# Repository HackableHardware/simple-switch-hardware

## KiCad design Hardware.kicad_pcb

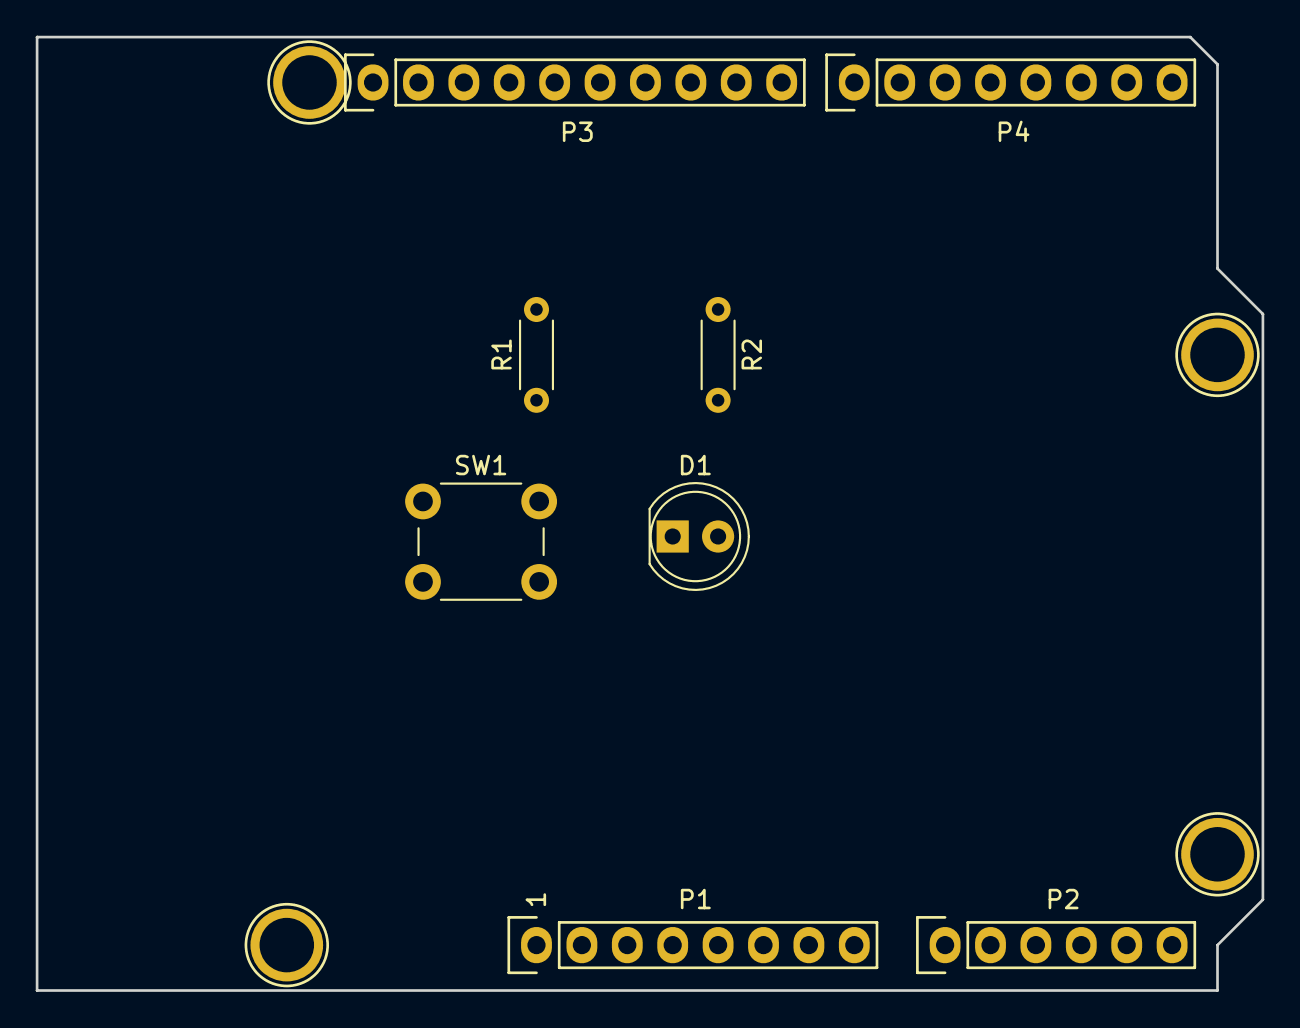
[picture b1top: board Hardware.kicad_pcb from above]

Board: 2 copper layers, 68.6 x 53.3 mm, 12 parts (0 on the bottom side), 5 nets, no tracks yet.

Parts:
D1: LED; LED_D5.0mm
P1: Power; Socket_Strip_Arduino_1x08
P2: Analog; Socket_Strip_Arduino_1x06
P3: Digital; Socket_Strip_Arduino_1x10
P4: Digital; Socket_Strip_Arduino_1x08
P5, P6, P7, P8: CONN_01X01; Arduino_1pin
R1: 10K; R_Axial_DIN0204_L3.6mm_D1.6mm_P5.08mm_Horizontal
R2: 100; R_Axial_DIN0204_L3.6mm_D1.6mm_P5.08mm_Horizontal
SW1: SW_Push; SW_PUSH_6mm_H7.3mm

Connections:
+5V: P1.5, SW1.2
/8: P3.10, R1.1, SW1.1
/9(**): P3.9, R2.1
GND: D1.1, P1.6, P1.7, P3.4, R1.2
unnamed: D1.2, R2.2

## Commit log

2018-09-10 Fix some mistakes in schematic
    This change fixes some mistakes made in the schematics view of the breadboard
    connections. There are some other cleanups to perform, but this one was
    essential.
2018-09-26 Hardware initial commit
    Initial commit of hardware project for sample led switch.
